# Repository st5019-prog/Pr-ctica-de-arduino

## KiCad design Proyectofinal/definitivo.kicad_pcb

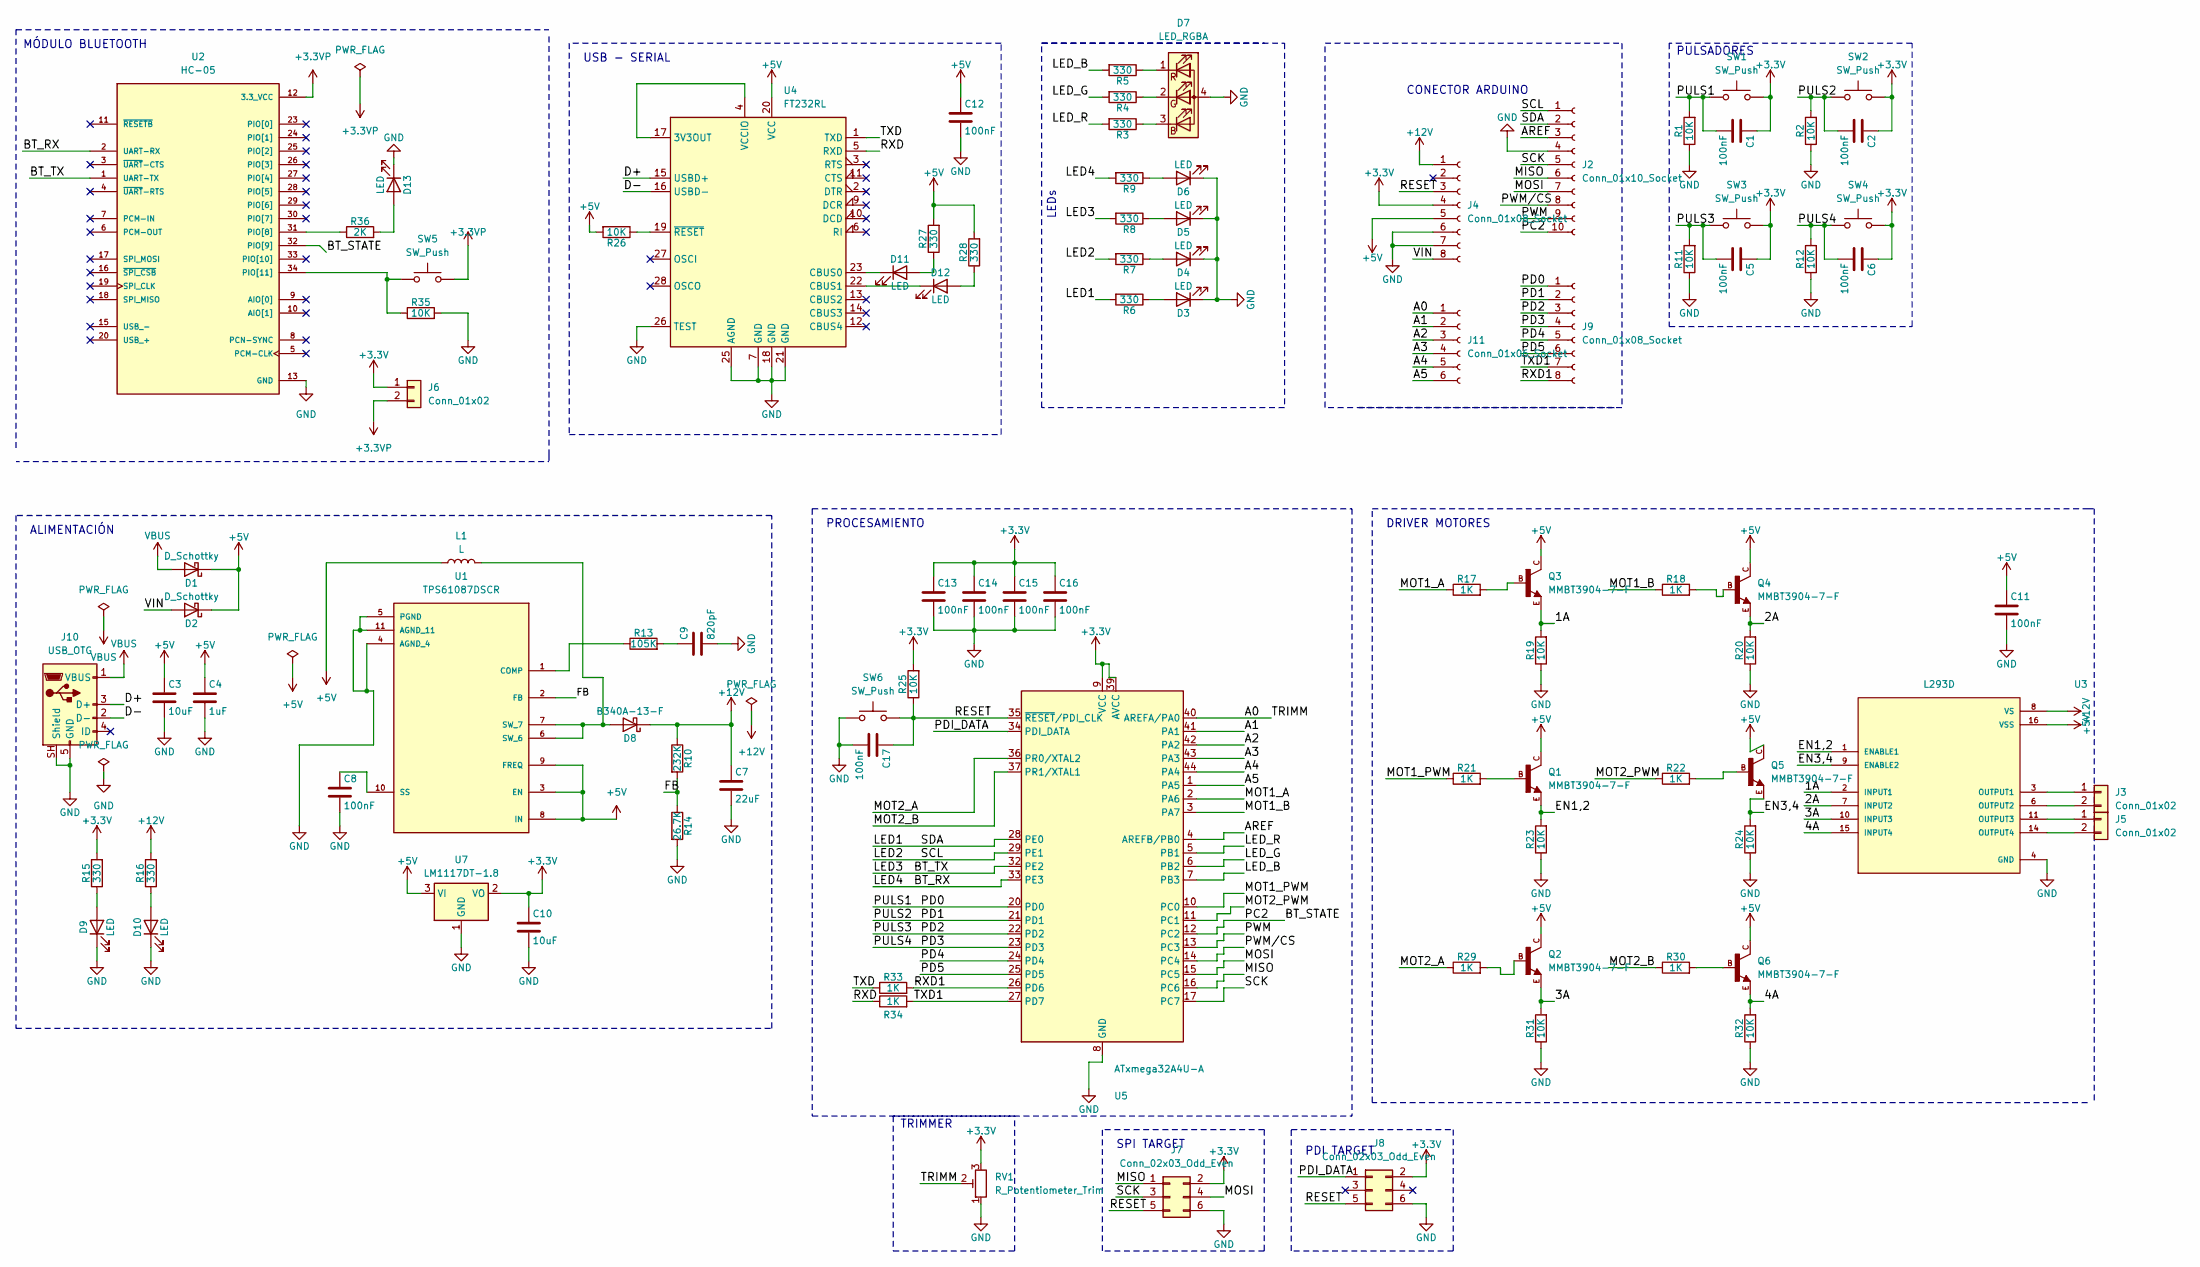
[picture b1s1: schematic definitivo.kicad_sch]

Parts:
C1, C2, C5, C6, C8, C11, C12, C13, C14, C15, C16: 100nF; C_0805_2012Metric
C3, C10: 10uF; C_Elec_4x5.4
C4: 1uF; C_0805_2012Metric
C7: 22uF; C_Elec_4x5.4
C9: 820pF; C_0805_2012Metric
C17: 100nF; C_Elec_4x5.4
D1, D2: D_Schottky; D_SOD-523
D3, D4, D5, D6, D9, D10, D11, D12, D13: LED; LED_0805_2012Metric
D7: LED_RGBA; LED_RGB_5050-6
D8: B340A-13-F; D_SOD-523
J2: Conn_01x10_Socket; PinSocket_1x10_P2.54mm_Vertical
J3, J5, J6: Conn_01x02; PinHeader_1x02_P2.54mm_Vertical
J4: Conn_01x08_Socket; PinSocket_1x08_P2.54mm_Vertical
J7, J8: Conn_02x03_Odd_Even; PinHeader_2x03_P2.54mm_Vertical
J9: Conn_01x08_Socket; PinSocket_1x08_P2.00mm_Vertical
J10: USB_OTG; USB_Micro-B_Amphenol_10103594-0001LF_Horizontal
J11: Conn_01x06_Socket; PinSocket_1x06_P2.54mm_Vertical
L1: L; L_1210_3225Metric
Q1, Q2, Q3, Q4, Q5, Q6: MMBT3904-7-F; SOT95P230X110-3N
R1, R2, R11, R12, R19, R20, R23, R24, R25, R26, R31, R32, R35: 10K; R_1206_3216Metric
R3, R4, R5, R6, R7, R8, R9, R15, R16, R27, R28: 330; R_1206_3216Metric
R10: 232K; R_1206_3216Metric
R13: 105K; R_1206_3216Metric
R14: 26.7K; R_1206_3216Metric
R17, R18, R21, R22, R29, R30, R33, R34: 1K; R_1206_3216Metric
R36: 2K; R_1206_3216Metric
RV1: R_Potentiometer_Trim; R_Array_SIP4
SW1, SW2, SW3, SW4, SW5, SW6: SW_Push; SW_Push_1P1T_NO_CK_KSC6xxG
U1: TPS61087DSCR; IC_TPS61087DSCR; PARTREV A
U2: HC-05; XCVR_HC-05; PARTREV v1.0
U3: L293D; DIP880W50P254L2000H510Q16
U4: FT232RL; SSOP-28_5.3x10.2mm_P0.65mm
U5: ATxmega32A4U-A; TQFP-44_10x10mm_P0.8mm
U7: LM1117DT-1.8; TO-252-3_TabPin2

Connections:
+3.3V: C1.1, C2.1, C5.1, C6.1, C10.1, C13.1, C14.1, C15.1, C16.1, J4.4, J6.1, J7.2, J8.2, R15.2, R25.2, RV1.3, SW1.2, SW2.2, SW3.2, SW4.2, U5.9 (VCC), U5.19 (VCC), U5.31 (VCC), U5.39 (AVCC), U7.2 (VO)
+3.3VP: J6.2, SW5.2, U2.12 (3.3_VCC)
+5V: C3.1, C4.1, C11.1, C12.1, D1.1 (K), D2.1 (K), J4.5, L1.1, Q1.C, Q2.C, Q3.C, Q4.C, Q5.C, Q6.C, R26.2, R27.2, R28.2, U1.3 (EN), U1.8 (IN), U1.9 (FREQ), U3.16 (VSS), U4.20 (VCC), U7.3 (VI)
+12V: C7.1, D8.1 (K), J4.1, R10.1, R16.2, U3.8 (VS)
/1A: Q3.E, R19.2, U3.2 (INPUT1)
/2A: Q4.E, R20.2, U3.7 (INPUT2)
/3A: Q2.E, R31.2, U3.10 (INPUT3)
/4A: Q6.E, R32.2, U3.15 (INPUT4)
/A0: J11.1, RV1.2, U5.40 (AREFA/PA0)
/A1: J11.2, U5.41 (PA1)
/A2: J11.3, U5.42 (PA2)
/A3: J11.4, U5.43 (PA3)
/A4: J11.5, U5.44 (PA4)
/A5: J11.6, U5.1 (PA5)
/AREF: J2.3, U5.4 (AREFB/PB0)
/BT_RX: R9.2, U2.2 (UART-RX), U5.33 (PE3)
/BT_STATE: J2.10, U2.32 (PIO[9]), U5.12 (PC2)
/BT_TX: R8.2, U2.1 (UART-TX), U5.32 (PE2)
/D+: J10.3 (D+), U4.15 (USBD+)
/D-: J10.2 (D-), U4.16 (USBD-)
/EN1,2: Q1.E, R23.2, U3.1 (ENABLE1)
/EN3,4: Q5.E, R24.2, U3.9 (ENABLE2)
/FB: R10.2, R14.1, U1.2 (FB)
/LED1: J2.2, R6.2, U5.28 (PE0)
/LED2: J2.1, R7.2, U5.29 (PE1)
/LED_B: R5.2, U5.7 (PB3)
/LED_G: R4.2, U5.6 (PB2)
/LED_R: R3.2, U5.5 (PB1)
/MISO: J2.6, J7.1, U5.16 (PC6)
/MOSI: J2.7, J7.4, U5.15 (PC5)
/MOT1_A: R17.1, U5.2 (PA6)
/MOT1_B: R18.1, U5.3 (PA7)
/MOT1_PWM: R21.1, U5.10 (PC0)
/MOT2_A: R29.1, U5.36 (PR0/XTAL2)
/MOT2_B: R30.1, U5.37 (PR1/XTAL1)
/MOT2_PWM: R22.1, U5.11 (PC1)
/PD0: C1.2, J9.1, R1.2, SW1.1, U5.20 (PD0)
/PD1: C2.2, J9.2, R2.2, SW2.1, U5.21 (PD1)
/PD2: C5.2, J9.3, R11.2, SW3.1, U5.22 (PD2)
/PD3: C6.2, J9.4, R12.2, SW4.1, U5.23 (PD3)
/PD4: J9.5, U5.24 (PD4)
/PD5: J9.6, U5.25 (PD5)
/PDI_DATA: J8.1, U5.34 (PDI_DATA)
/PWM: J2.9, U5.13 (PC3)
/PWM/CS: J2.8, U5.14 (PC4)
/RESET: C17.1, J4.3, J7.5, J8.5, R25.1, SW6.2, U5.35 (~RESET/PDI_CLK)
/RXD: R34.1, U4.5 (RXD)
/RXD1: J9.8, R33.2, U5.26 (PD6)
/SCK: J2.5, J7.3, U5.17 (PC7)
/TXD: R33.1, U4.1 (TXD)
/TXD1: J9.7, R34.2, U5.27 (PD7)
/VIN: D2.2 (A), J4.8
GND: C3.2, C4.2, C7.2, C8.2, C9.2, C10.2, C11.2, C12.2, C13.2, C14.2, C15.2, C16.2, C17.2, D3.1 (K), D4.1 (K), D5.1 (K), D6.1 (K), D7.4 (A), D9.1 (K), D10.1 (K), D13.1 (K), J2.4, J4.6, J4.7, J7.6, J8.6, J10.5 (GND), J10.SH (Shield), R1.1, R2.1, R11.1, R12.1, R14.2, R19.1, R20.1, R23.1, R24.1, R31.1, R32.1, R35.2, RV1.1, SW6.1, U1.4 (AGND_4), U1.5 (PGND), U1.11 (AGND_11), U2.13 (GND), U2.21 (GND), U2.22 (GND), U3.4 (GND), U3.5 (GND), U3.12 (GND), U3.13 (GND), U4.7 (GND), U4.18 (GND), U4.21 (GND), U4.25 (AGND), U4.26 (TEST), U5.8 (GND), U5.18 (GND), U5.30 (GND), U5.38 (GND), U7.1 (GND)
unnamed: C9.1, R13.2
unnamed: D3.2 (A), R6.1
unnamed: D4.2 (A), R7.1
unnamed: D5.2 (A), R8.1
unnamed: D6.2 (A), R9.1
unnamed: D7.3 (BK), R3.1
unnamed: D7.2 (GK), R4.1
unnamed: D7.1 (RK), R5.1
unnamed: D8.2 (A), L1.2, U1.6 (SW_6), U1.7 (SW_7)
unnamed: D9.2 (A), R15.1
unnamed: D10.2 (A), R16.1
unnamed: D11.2 (A), R27.1
unnamed: D11.1 (K), U4.23 (CBUS0)
unnamed: D12.2 (A), R28.1
unnamed: D12.1 (K), U4.22 (CBUS1)
unnamed: D13.2 (A), R36.2
unnamed: J3.1, U3.3 (OUTPUT1)
unnamed: J3.2, U3.6 (OUTPUT2)
unnamed: J5.1, U3.11 (OUTPUT3)
unnamed: J5.2, U3.14 (OUTPUT4)
unnamed: Q1.B, R21.2
unnamed: Q2.B, R29.2
unnamed: Q3.B, R17.2
unnamed: Q4.B, R18.2
unnamed: Q5.B, R22.2
unnamed: Q6.B, R30.2
unnamed: R13.1, U1.1 (COMP)
unnamed: C8.1, U1.10 (SS)
unnamed: R36.1, U2.31 (PIO[8])
unnamed: R35.1, SW5.1, U2.34 (PIO[11])
unnamed: U4.4 (VCCIO), U4.17 (3V3OUT)
unnamed: R26.1, U4.19 (~RESET)
VBUS: D1.2 (A), J10.1 (VBUS)

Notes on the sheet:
TRIMMER
ALIMENTACIÓN
PROCESAMIENTO
PDI TARGET
PULSADORES
USB - SERIAL
CONECTOR ARDUINO
DRIVER MOTORES
SPI TARGET
LEDs
MÓDULO BLUETOOTH

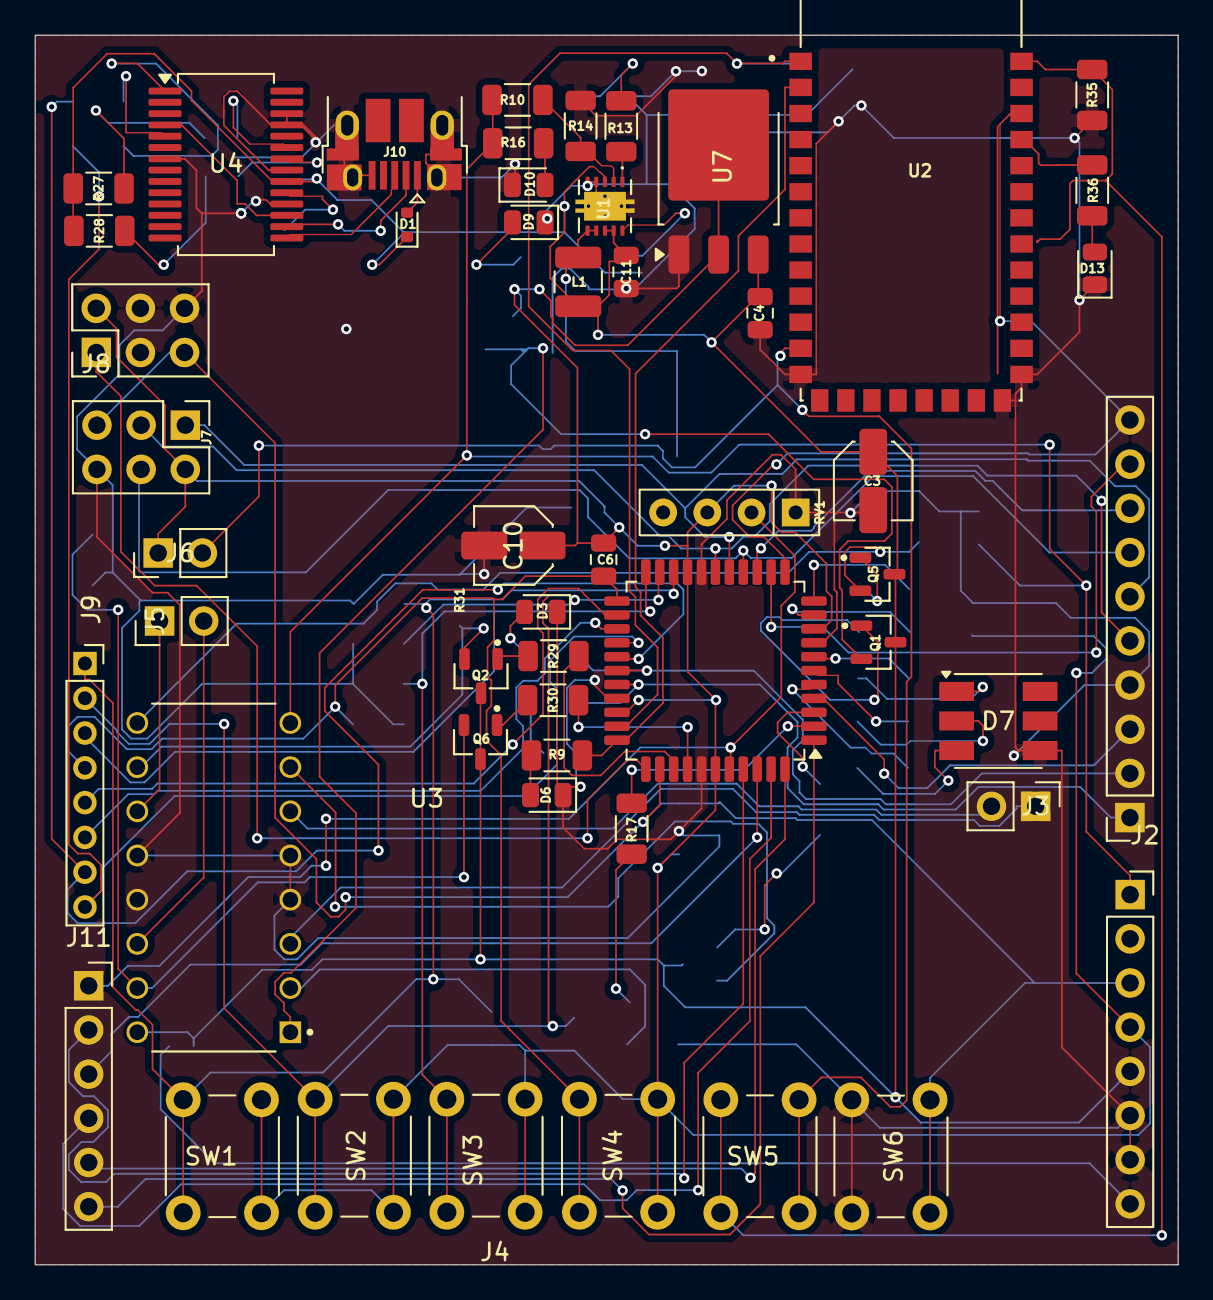
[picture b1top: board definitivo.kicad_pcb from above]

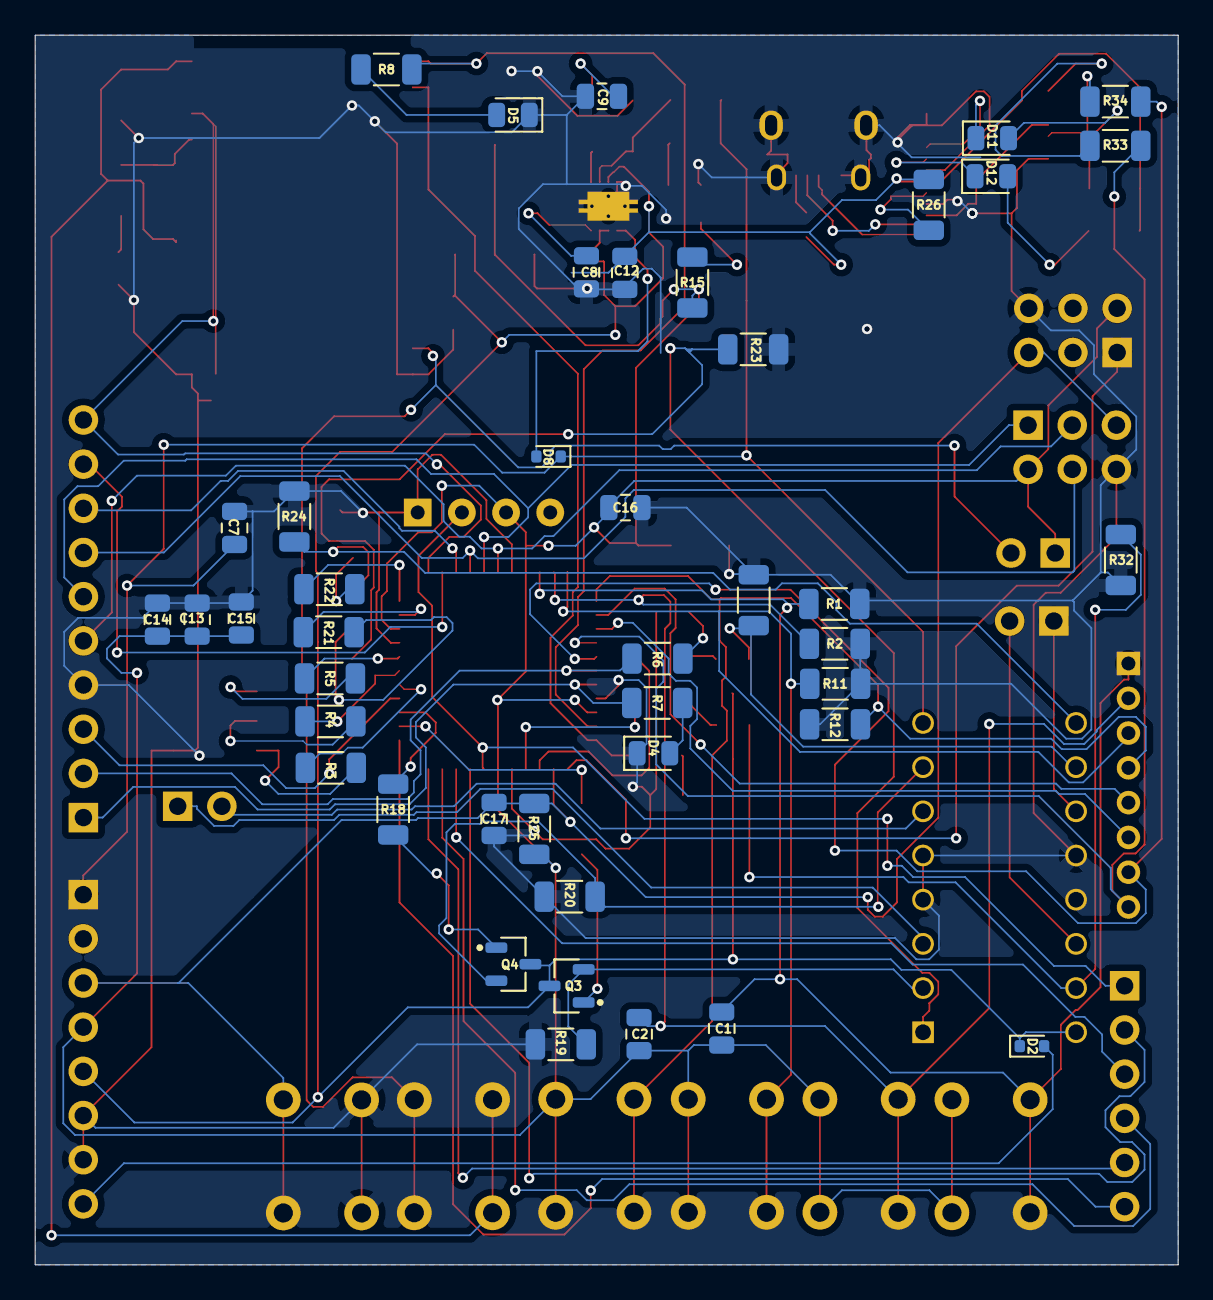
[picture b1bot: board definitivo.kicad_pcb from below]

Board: 2 copper layers, 65.7 x 70.7 mm, 95 parts (43 on the bottom side), 86 nets.
